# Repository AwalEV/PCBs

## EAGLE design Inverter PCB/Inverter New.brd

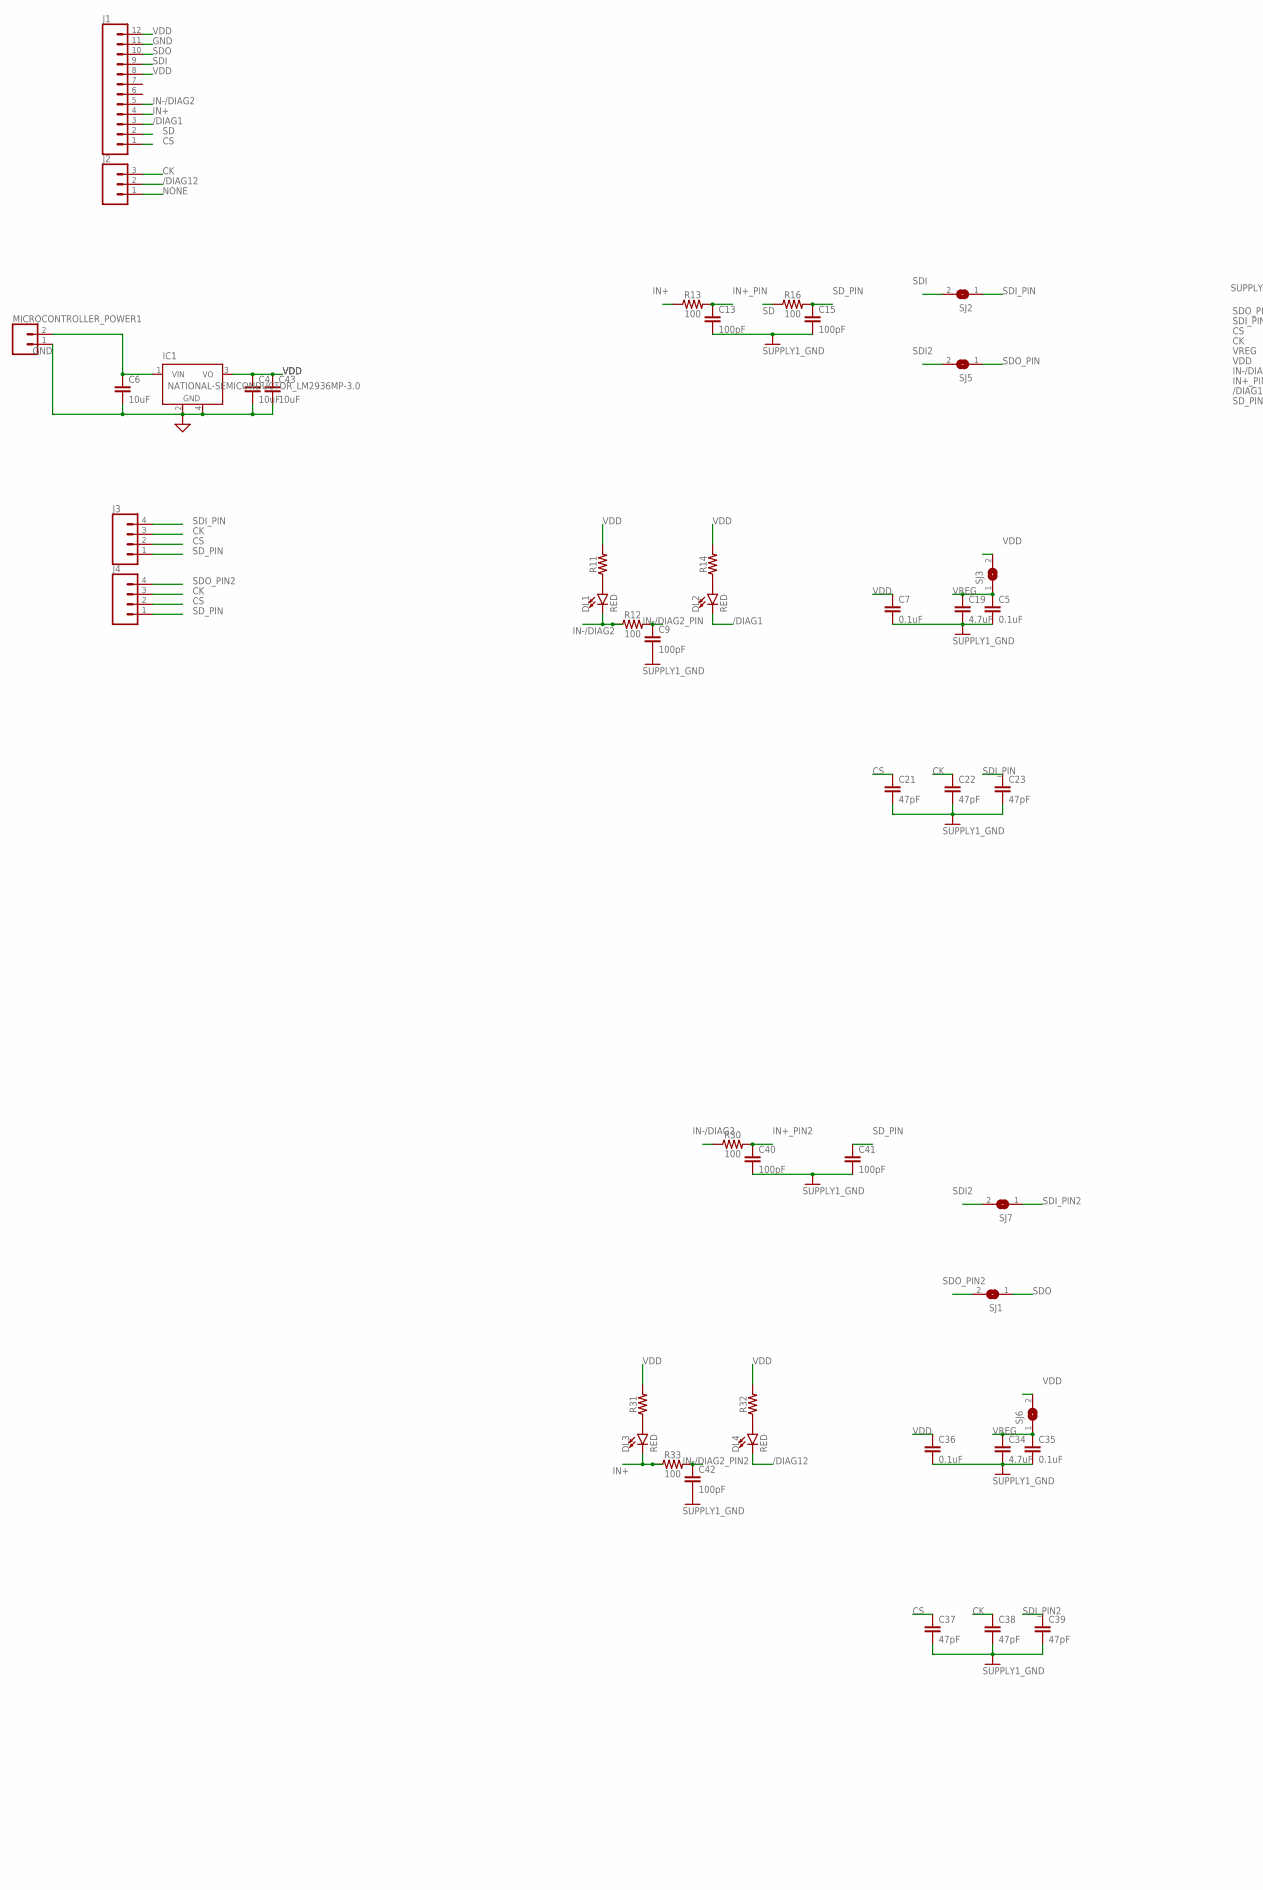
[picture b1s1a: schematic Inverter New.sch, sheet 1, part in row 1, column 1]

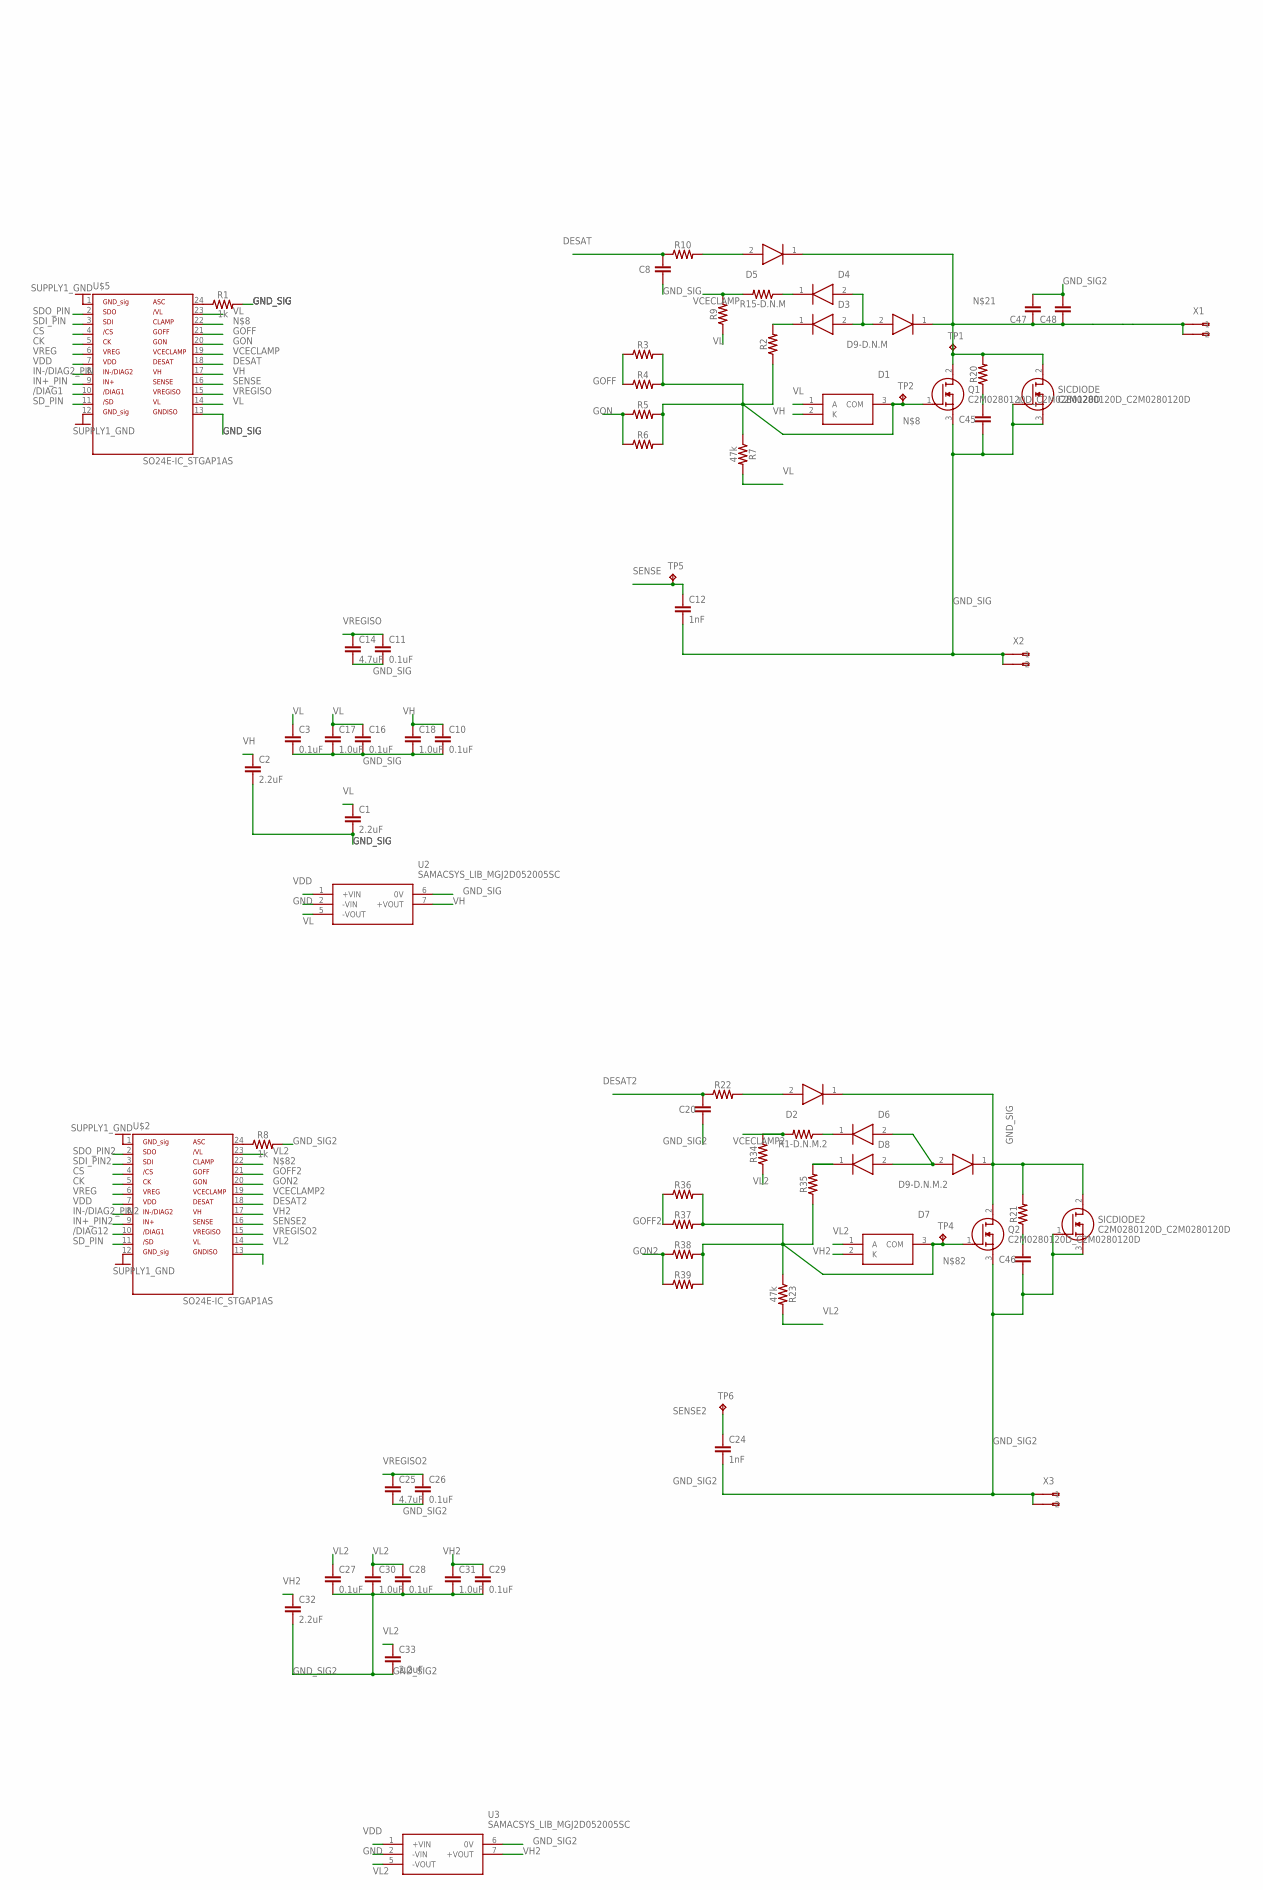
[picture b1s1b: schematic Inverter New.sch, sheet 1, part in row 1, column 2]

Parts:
C1, C2, C32, C33: 2.2uF; SPARKFUN-CAPACITORS_1206
C3, C5, C7, C10, C11, C16, C26, C27, C28, C29, C35, C36: 0.1uF; SPARKFUN-CAPACITORS_0603
C4, C6, C43: 10uF; SPARKFUN-CAPACITORS_1210
C8, C9, C13, C15, C20, C40, C41, C42, C45, C46: 100pF; SPARKFUN-CAPACITORS_0603
C12, C24: 1nF; SPARKFUN-CAPACITORS_0603
C14, C19, C25, C34: 4.7uF; SPARKFUN-CAPACITORS_0603
C17, C18, C30, C31: 1.0uF; SPARKFUN-CAPACITORS_0805
C21, C22, C23, C37, C38, C39: 47pF; SPARKFUN-CAPACITORS_0603
C47, C48: C-EU225-062X268; C225-062X268
D1, D7: BAT54SFILM_BAT54SFILM; BAT54SFILM_SOT105P242X150-3N
D2, D5: STTH112A_STTH112A; STTH112A_DIOM5126X265N
D3, D8, D9-D.N.M, D9-D.N.M.2: STPS2H100A_STPS2H100A; STPS2H100A_DIOM5126X265N
D4, D6: BAT20JFILM_BAT20JFILM; BAT20JFILM_SOD2512X113N
DL1, DL2, DL3, DL4: RED; SPARKFUN-LED_LED-1206
IC1: NATIONAL-SEMICONDUCTOR_LM2936MP-3.0; NATIONAL-SEMICONDUCTOR_SOT223
J1: SPARKFUN-CONNECTORS_CONN_12LONGPADS; SPARKFUN-CONNECTORS_1X12_LONGPADS
J2: SPARKFUN-CONNECTORS_CONN_03LONGPADS; SPARKFUN-CONNECTORS_1X03_LONGPADS
J3, J4: SPARKFUN-CONNECTORS_CONN_04LONGPADS; SPARKFUN-CONNECTORS_1X04_LONGPADS
MICROCONTROLLER_POWER1: SPARKFUN-CONNECTORS_CONN_025MM; SPARKFUN-CONNECTORS_SCREWTERMINAL-5MM-2
Q1, Q2: C2M0280120D_C2M0280120D; C2M0280120D_TO544P521X1594X2550-3P
R1, R8, R10, R22: 1k; SPARKFUN-RESISTORS_0603
R1-D.N.M.2, R9, R15-D.N.M, R34: 0; SPARKFUN-RESISTORS_0603
R2, R35: SPARKFUN-RESISTORS_0805
R3, R4, R5, R6, R20, R21, R36, R37, R38, R39: SPARKFUN-RESISTORS_1206
R7, R23: 47k; SPARKFUN-RESISTORS_0603
R11, R14, R31, R32: SPARKFUN-RESISTORS_0603
R12, R13, R16, R30, R33: 100; SPARKFUN-RESISTORS_0603
SICDIODE, SICDIODE2: C2M0280120D_C2M0280120D; C2M0280120D_TO544P521X1594X2550-3P
SJ1, SJ2, SJ3, SJ5, SJ6, SJ7: JUMPER_SJ
TP1, TP2, TP4, TP5, TP6: TPTP15SQ; TP15SQ
U2, U3: SAMACSYS_LIB_MGJ2D052005SC; SAMACSYS_LIB_MGJ2D_7-PIN-SIP
U$2, U$5: SO24E-IC_STGAP1AS; SO24E-IC_SO24W
X1, X2, X3: 234-502

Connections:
/DIAG1: DL2.C, J1.3, U$5.10 (/DIAG1)
/DIAG12: DL4.C, J2.2, U$2.10 (/DIAG1)
CK: C22.1, C38.1, J2.3, J3.3, J4.3, U$2.5 (CK), U$5.5 (CK)
CS: C21.1, C37.1, J1.1, J3.2, J4.2, U$2.4 (/CS), U$5.4 (/CS)
DESAT: C8.1, R10.1, U$5.18 (DESAT)
DESAT2: C20.1, R22.1, U$2.18 (DESAT)
GND: C4.2, C5.2, C6.2, C7.2, C9.2, C13.2, C15.2, C19.2, C21.2, C22.2, C23.2, C34.2, C35.2, C36.2, C37.2, C38.2, C39.2, C40.2, C41.2, C42.2, C43.2, IC1.2 (GND), IC1.4 (GND), J1.11, MICROCONTROLLER_POWER1.1, U2.2 (-VIN), U3.2 (-VIN), U$2.1 (GND_SIG), U$2.12 (GND_SIG), U$5.1 (GND_SIG), U$5.12 (GND_SIG); also elsewhere on the board
GND_SIG: C1.2, C2.2, C3.2, C8.2, C10.2, C11.2, C12.2, C14.2, C16.2, C17.2, C18.2, C45.2, D2.1 (K), D9-D.N.M.2.1 (K), Q1.3 (S), Q2.2 (D), R1.2, R21.2, SICDIODE.1 (G), SICDIODE.3 (S), SICDIODE2.2 (D), U2.6 (0V), U$5.13 (GNDISO), X2.A1 (-1), X2.A2 (-2)
GND_SIG2: C20.2, C24.2, C25.2, C26.2, C27.2, C28.2, C29.2, C30.2, C31.2, C32.2, C33.2, C46.2, C47.2, C48.2, Q2.3 (S), R8.2, SICDIODE2.1 (G), SICDIODE2.3 (S), U3.6 (0V), U$2.13 (GNDISO), X3.A1 (-1), X3.A2 (-2)
GOFF: R3.1, R4.1, U$5.21 (GOFF)
GOFF2: R36.1, R37.1, U$2.21 (GOFF)
GON: R5.1, R6.1, U$5.20 (GON)
GON2: R38.1, R39.1, U$2.20 (GON)
IN+: DL3.C, J1.4, R13.1, R33.1
IN+_PIN: C13.1, R13.2, U$5.9 (IN+)
IN+_PIN2: C40.1, R30.2, U$2.9 (IN+)
IN-/DIAG2: DL1.C, J1.5, R12.1, R30.1
IN-/DIAG2_PIN: C9.1, R12.2, U$5.8 (IN-/DIAG2)
IN-/DIAG2_PIN2: C42.1, R33.2, U$2.8 (IN-/DIAG2)
unnamed: R1.1, U$5.24 (ASC)
unnamed: DL1.A, R11.1
unnamed: DL2.A, R14.1
unnamed: D5.2 (A), R10.2
unnamed: D2.2 (A), R22.2
unnamed: D3.1 (K), R2.2
unnamed: D1.3 (COM), Q1.1 (G), R2.1, R3.2, R4.2, R5.2, R6.2, R7.1, TP2.TP, U$5.22 (CLAMP)
unnamed: C6.1, IC1.1 (VIN), MICROCONTROLLER_POWER1.2
unnamed: D8.1 (K), R35.2
unnamed: R8.1, U$2.24 (ASC)
unnamed: DL3.A, R31.1
unnamed: DL4.A, R32.1
unnamed: D4.1 (K), R15-D.N.M.1
unnamed: D3.2 (A), D4.2 (A), D9-D.N.M.2 (A)
unnamed: D6.1 (K), R1-D.N.M.2.1
unnamed: D6.2 (A), D8.2 (A), D9-D.N.M.2.2 (A)
unnamed: C47.1, C48.1, D5.1 (K), D9-D.N.M.1 (K), Q1.2 (D), R20.2, SICDIODE.2 (D), TP1.TP, X1.A1 (-1), X1.A2 (-2)
unnamed: C45.1, R20.1
unnamed: C46.1, R21.1
unnamed: D7.3 (COM), Q2.1 (G), R23.1, R35.1, R36.2, R37.2, R38.2, R39.2, TP4.TP, U$2.22 (CLAMP)
NONE: J2.1
SD: J1.2, R16.1
SDI: J1.9, SJ2.2
SDI2: SJ5.2, SJ7.2
SDI_PIN: C23.1, J3.4, SJ2.1, U$5.3 (SDI)
SDI_PIN2: C39.1, SJ7.1, U$2.3 (SDI)
SDO: J1.10, SJ1.1
SDO_PIN: SJ5.1, U$5.2 (SDO)
SDO_PIN2: J4.4, SJ1.2, U$2.2 (SDO); also elsewhere on the board
SD_PIN: C15.1, C41.1, J3.1, J4.1, R16.2, U$2.11 (/SD), U$5.11 (/SD)
SENSE: C12.1, TP5.TP, U$5.16 (SENSE)
SENSE2: C24.1, TP6.TP, U$2.16 (SENSE)
VCECLAMP: R9.2, R15-D.N.M.2, U$5.19 (VCECLAMP)
VCECLAMP2: R1-D.N.M.2.2, R34.2, U$2.19 (VCECLAMP)
VDD: C4.1, C7.1, C36.1, C43.1, IC1.3 (VO), J1.8, J1.12, R11.2, R14.2, R31.2, R32.2, SJ3.2, SJ6.2, U2.1 (+VIN), U3.1 (+VIN), U$2.7 (VDD), U$5.7 (VDD); also elsewhere on the board
VH: C2.1, C10.1, C18.1, D1.2 (K), U2.7 (+VOUT), U$5.17 (VH)
VH2: C29.1, C31.1, C32.1, D7.2 (K), U3.7 (+VOUT), U$2.17 (VH)
VL: C1.1, C3.1, C16.1, C17.1, D1.1 (A), R7.2, R9.1, U2.5 (-VOUT), U$5.14 (VL), U$5.23 (VL)
VL2: C27.1, C28.1, C30.1, C33.1, D7.1 (A), R23.2, R34.1, U3.5 (-VOUT), U$2.14 (VL), U$2.23 (VL)
VREG: C5.1, C19.1, C34.1, C35.1, SJ3.1, SJ6.1, U$2.6 (VREG), U$5.6 (VREG)
VREGISO: C11.1, C14.1, U$5.15 (VREGISO)
VREGISO2: C25.1, C26.1, U$2.15 (VREGISO)

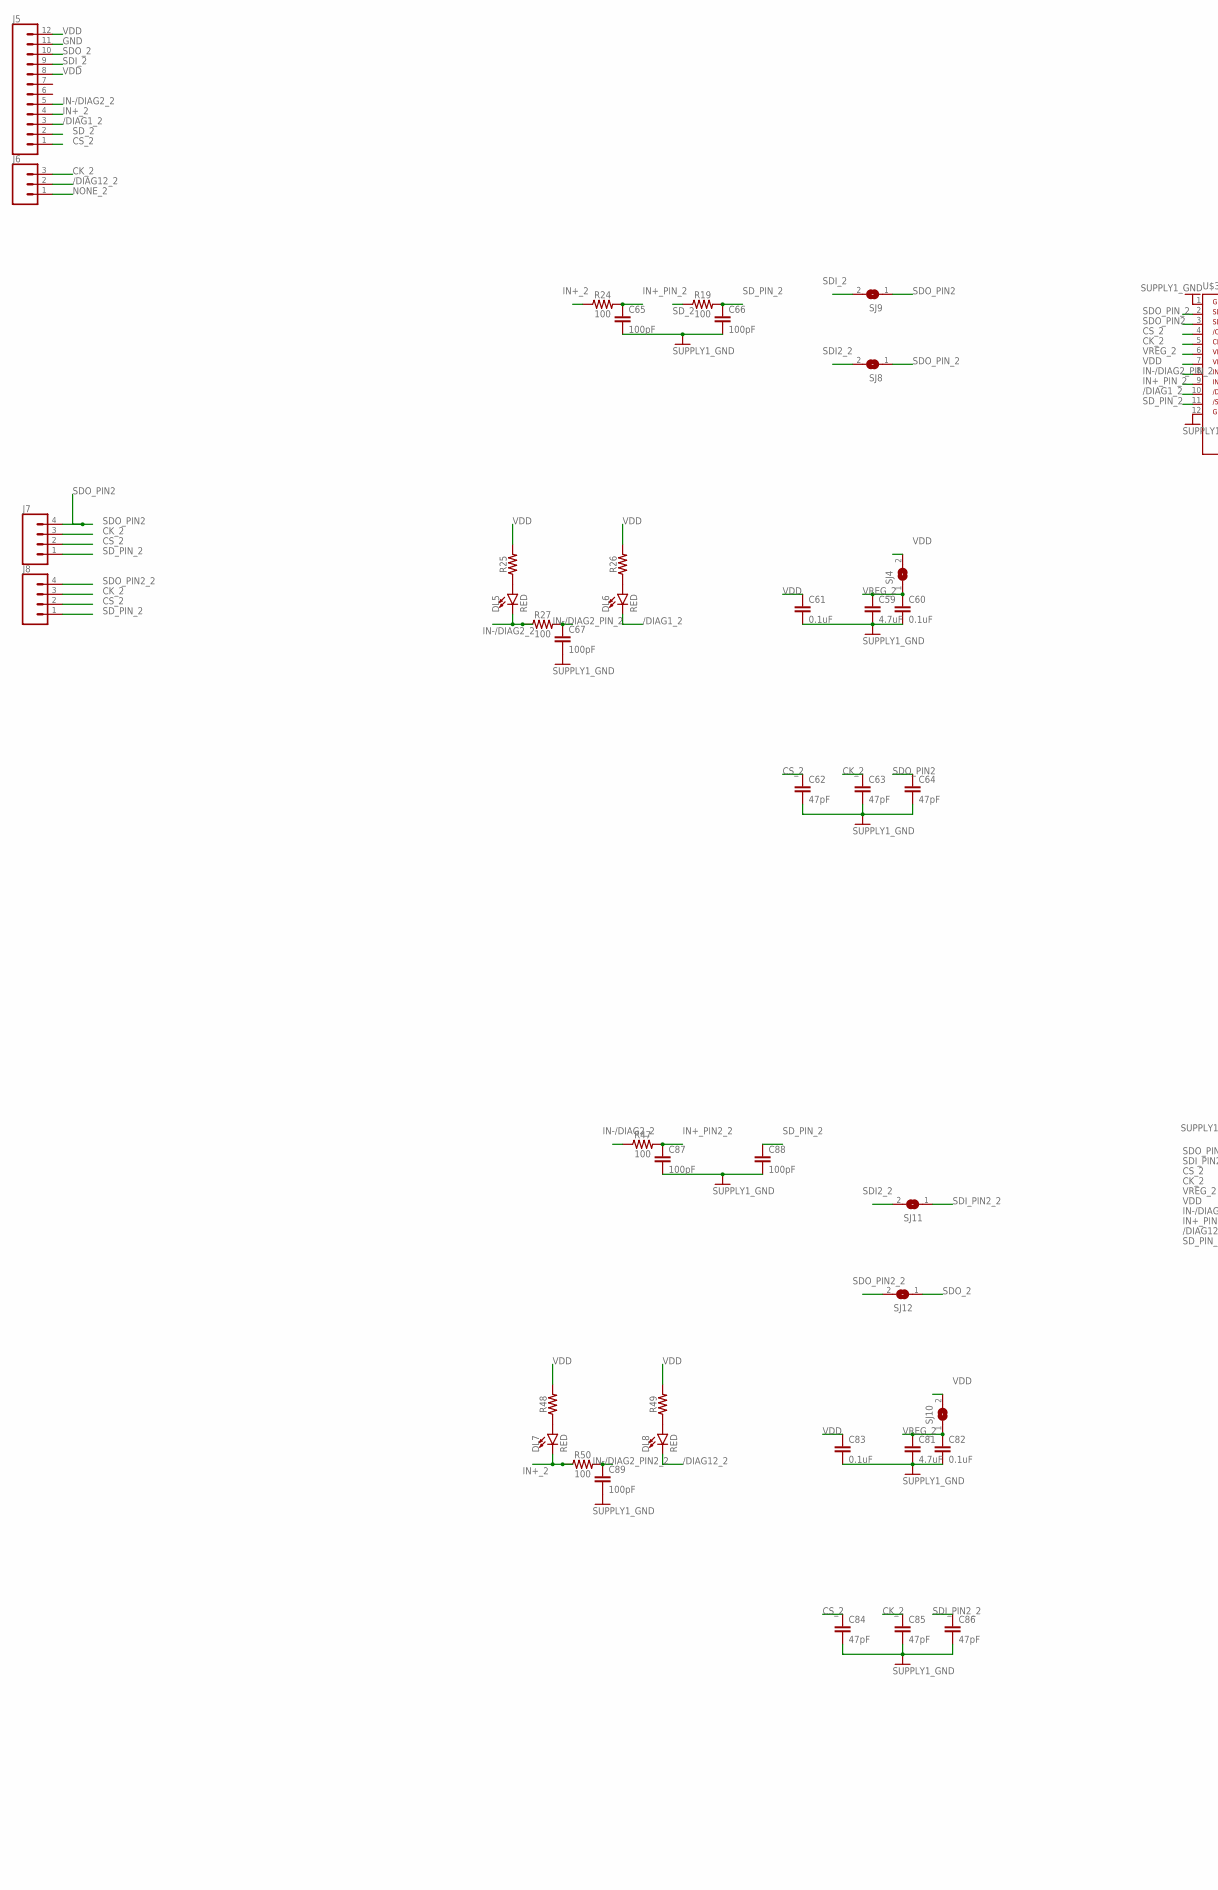
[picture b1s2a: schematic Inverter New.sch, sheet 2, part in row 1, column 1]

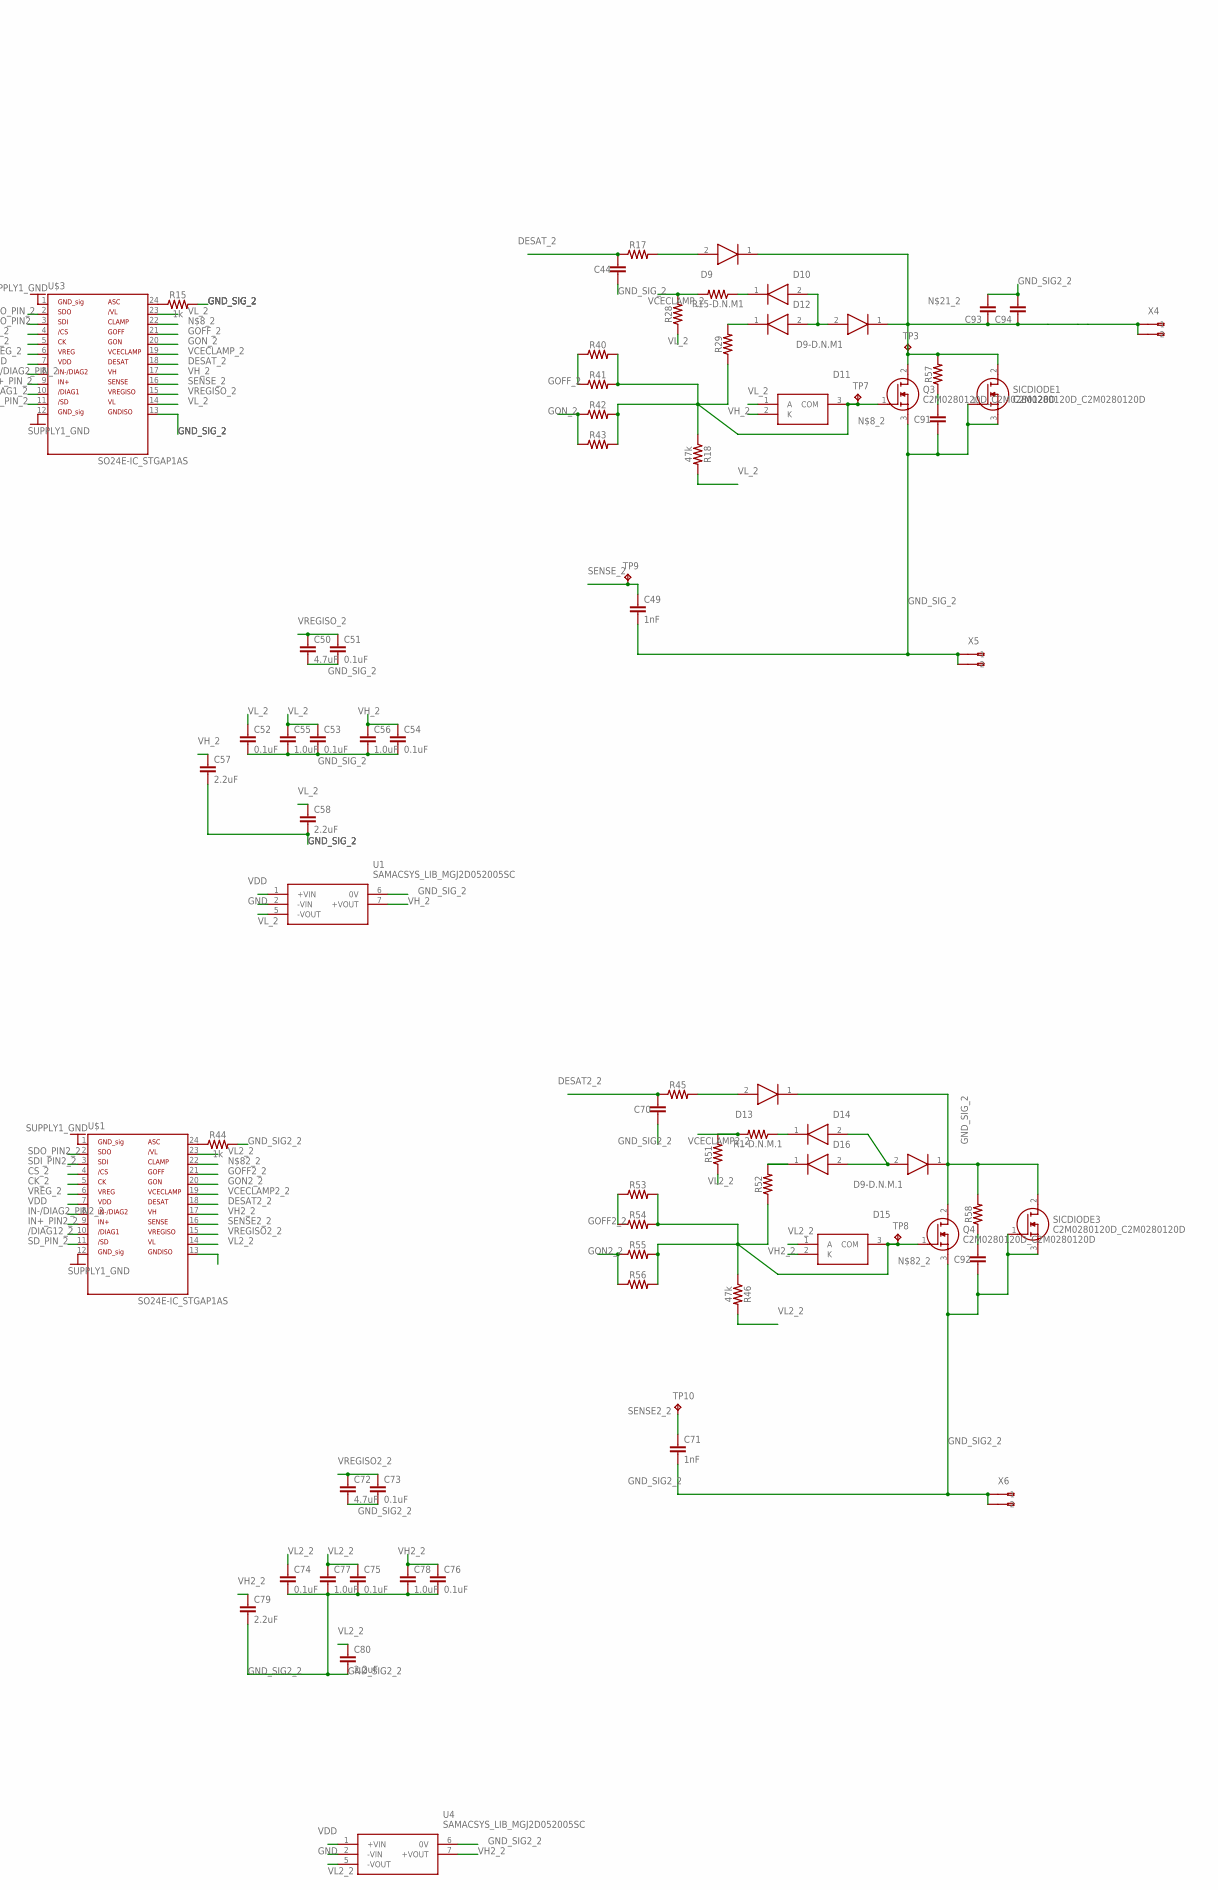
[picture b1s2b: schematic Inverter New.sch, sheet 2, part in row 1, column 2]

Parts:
C44, C65, C66, C67, C70, C87, C88, C89, C91, C92: 100pF; SPARKFUN-CAPACITORS_0603
C49, C71: 1nF; SPARKFUN-CAPACITORS_0603
C50, C59, C72, C81: 4.7uF; SPARKFUN-CAPACITORS_0603
C51, C52, C53, C54, C60, C61, C73, C74, C75, C76, C82, C83: 0.1uF; SPARKFUN-CAPACITORS_0603
C55, C56, C77, C78: 1.0uF; SPARKFUN-CAPACITORS_0805
C57, C58, C79, C80: 2.2uF; SPARKFUN-CAPACITORS_1206
C62, C63, C64, C84, C85, C86: 47pF; SPARKFUN-CAPACITORS_0603
C93, C94: C-EU225-062X268; C225-062X268
D9, D13: STTH112A_STTH112A; STTH112A_DIOM5126X265N
D9-D.N.M1, D9-D.N.M.1, D12, D16: STPS2H100A_STPS2H100A; STPS2H100A_DIOM5126X265N
D10, D14: BAT20JFILM_BAT20JFILM; BAT20JFILM_SOD2512X113N
D11, D15: BAT54SFILM_BAT54SFILM; BAT54SFILM_SOT105P242X150-3N
DL5, DL6, DL7, DL8: RED; SPARKFUN-LED_LED-1206
J5: SPARKFUN-CONNECTORS_CONN_12LONGPADS; SPARKFUN-CONNECTORS_1X12_LONGPADS
J6: SPARKFUN-CONNECTORS_CONN_03LONGPADS; SPARKFUN-CONNECTORS_1X03_LONGPADS
J7, J8: SPARKFUN-CONNECTORS_CONN_04LONGPADS; SPARKFUN-CONNECTORS_1X04_LONGPADS
Q3, Q4: C2M0280120D_C2M0280120D; C2M0280120D_TO544P521X1594X2550-3P
R1-D.N.M.1, R15-D.N.M1, R28, R51: 0; SPARKFUN-RESISTORS_0603
R15, R17, R44, R45: 1k; SPARKFUN-RESISTORS_0603
R18, R46: 47k; SPARKFUN-RESISTORS_0603
R19, R24, R27, R47, R50: 100; SPARKFUN-RESISTORS_0603
R25, R26, R48, R49: SPARKFUN-RESISTORS_0603
R29, R52: SPARKFUN-RESISTORS_0805
R40, R41, R42, R43, R53, R54, R55, R56, R57, R58: SPARKFUN-RESISTORS_1206
SICDIODE1, SICDIODE3: C2M0280120D_C2M0280120D; C2M0280120D_TO544P521X1594X2550-3P
SJ4, SJ8, SJ9, SJ10, SJ11, SJ12: JUMPER_SJ
TP3, TP7, TP8, TP9, TP10: TPTP15SQ; TP15SQ
U1, U4: SAMACSYS_LIB_MGJ2D052005SC; SAMACSYS_LIB_MGJ2D_7-PIN-SIP
U$1, U$3: SO24E-IC_STGAP1AS; SO24E-IC_SO24W
X4, X5, X6: 234-502

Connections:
/DIAG1_2: DL6.C, J5.3, U$3.10 (/DIAG1)
/DIAG12_2: DL8.C, J6.2, U$1.10 (/DIAG1)
CK_2: C63.1, C85.1, J6.3, J7.3, J8.3, U$1.5 (CK), U$3.5 (CK)
CS_2: C62.1, C84.1, J5.1, J7.2, J8.2, U$1.4 (/CS), U$3.4 (/CS)
DESAT2_2: C70.1, R45.1, U$1.18 (DESAT)
DESAT_2: C44.1, R17.1, U$3.18 (DESAT)
GND: C59.2, C60.2, C61.2, C62.2, C63.2, C64.2, C65.2, C66.2, C67.2, C81.2, C82.2, C83.2, C84.2, C85.2, C86.2, C87.2, C88.2, C89.2, J5.11, U1.2 (-VIN), U4.2 (-VIN), U$1.1 (GND_SIG), U$1.12 (GND_SIG), U$3.1 (GND_SIG), U$3.12 (GND_SIG); also elsewhere on the board
GND_SIG2_2: C70.2, C71.2, C72.2, C73.2, C74.2, C75.2, C76.2, C77.2, C78.2, C79.2, C80.2, C92.2, C93.2, C94.2, Q4.3 (S), R44.2, SICDIODE3.1 (G), SICDIODE3.3 (S), U4.6 (0V), U$1.13 (GNDISO), X6.A1 (-1), X6.A2 (-2)
GND_SIG_2: C44.2, C49.2, C50.2, C51.2, C52.2, C53.2, C54.2, C55.2, C56.2, C57.2, C58.2, C91.2, D9-D.N.M.1.1 (K), D13.1 (K), Q3.3 (S), Q4.2 (D), R15.2, R58.2, SICDIODE1.1 (G), SICDIODE1.3 (S), SICDIODE3.2 (D), U1.6 (0V), U$3.13 (GNDISO), X5.A1 (-1), X5.A2 (-2)
GOFF2_2: R53.1, R54.1, U$1.21 (GOFF)
GOFF_2: R40.1, R41.1, U$3.21 (GOFF)
GON2_2: R55.1, R56.1, U$1.20 (GON)
GON_2: R42.1, R43.1, U$3.20 (GON)
IN+_2: DL7.C, J5.4, R24.1, R50.1
IN+_PIN2_2: C87.1, R47.2, U$1.9 (IN+)
IN+_PIN_2: C65.1, R24.2, U$3.9 (IN+)
IN-/DIAG2_2: DL5.C, J5.5, R27.1, R47.1
IN-/DIAG2_PIN2_2: C89.1, R50.2, U$1.8 (IN-/DIAG2)
IN-/DIAG2_PIN_2: C67.1, R27.2, U$3.8 (IN-/DIAG2)
unnamed: D9.2 (A), R17.2
unnamed: D11.3 (COM), Q3.1 (G), R18.1, R29.1, R40.2, R41.2, R42.2, R43.2, TP7.TP, U$3.22 (CLAMP)
unnamed: D12.1 (K), R29.2
unnamed: DL5.A, R25.1
unnamed: C93.1, C94.1, D9.1 (K), D9-D.N.M1.1 (K), Q3.2 (D), R57.2, SICDIODE1.2 (D), TP3.TP, X4.A1 (-1), X4.A2 (-2)
unnamed: DL6.A, R26.1
unnamed: D13.2 (A), R45.2
unnamed: D16.1 (K), R52.2
unnamed: R44.1, U$1.24 (ASC)
unnamed: DL7.A, R48.1
unnamed: DL8.A, R49.1
unnamed: D9-D.N.M1.2 (A), D10.2 (A), D12.2 (A)
unnamed: D10.1 (K), R15-D.N.M1.1
unnamed: D9-D.N.M.1.2 (A), D14.2 (A), D16.2 (A)
unnamed: D14.1 (K), R1-D.N.M.1.1
unnamed: C91.1, R57.1
unnamed: C92.1, R58.1
unnamed: R15.1, U$3.24 (ASC)
unnamed: D15.3 (COM), Q4.1 (G), R46.1, R52.1, R53.2, R54.2, R55.2, R56.2, TP8.TP, U$1.22 (CLAMP)
NONE_2: J6.1
SDI2_2: SJ8.2, SJ11.2
SDI_2: J5.9, SJ9.2
SDI_PIN2_2: C86.1, SJ11.1, U$1.3 (SDI)
SDO_2: J5.10, SJ12.1
SDO_PIN2: C64.1, J7.4, SJ9.1, U$3.3 (SDI); also elsewhere on the board
SDO_PIN2_2: J8.4, SJ12.2, U$1.2 (SDO)
SDO_PIN_2: SJ8.1, U$3.2 (SDO)
SD_2: J5.2, R19.1
SD_PIN_2: C66.1, C88.1, J7.1, J8.1, R19.2, U$1.11 (/SD), U$3.11 (/SD)
SENSE2_2: C71.1, TP10.TP, U$1.16 (SENSE)
SENSE_2: C49.1, TP9.TP, U$3.16 (SENSE)
VCECLAMP2_2: R1-D.N.M.1.2, R51.2, U$1.19 (VCECLAMP)
VCECLAMP_2: R15-D.N.M1.2, R28.2, U$3.19 (VCECLAMP)
VDD: C61.1, C83.1, J5.8, J5.12, R25.2, R26.2, R48.2, R49.2, SJ4.2, SJ10.2, U1.1 (+VIN), U4.1 (+VIN), U$1.7 (VDD), U$3.7 (VDD); also elsewhere on the board
VH2_2: C76.1, C78.1, C79.1, D15.2 (K), U4.7 (+VOUT), U$1.17 (VH)
VH_2: C54.1, C56.1, C57.1, D11.2 (K), U1.7 (+VOUT), U$3.17 (VH)
VL2_2: C74.1, C75.1, C77.1, C80.1, D15.1 (A), R46.2, R51.1, U4.5 (-VOUT), U$1.14 (VL), U$1.23 (VL)
VL_2: C52.1, C53.1, C55.1, C58.1, D11.1 (A), R18.2, R28.1, U1.5 (-VOUT), U$3.14 (VL), U$3.23 (VL)
VREGISO2_2: C72.1, C73.1, U$1.15 (VREGISO)
VREGISO_2: C50.1, C51.1, U$3.15 (VREGISO)
VREG_2: C59.1, C60.1, C81.1, C82.1, SJ4.1, SJ10.1, U$1.6 (VREG), U$3.6 (VREG)

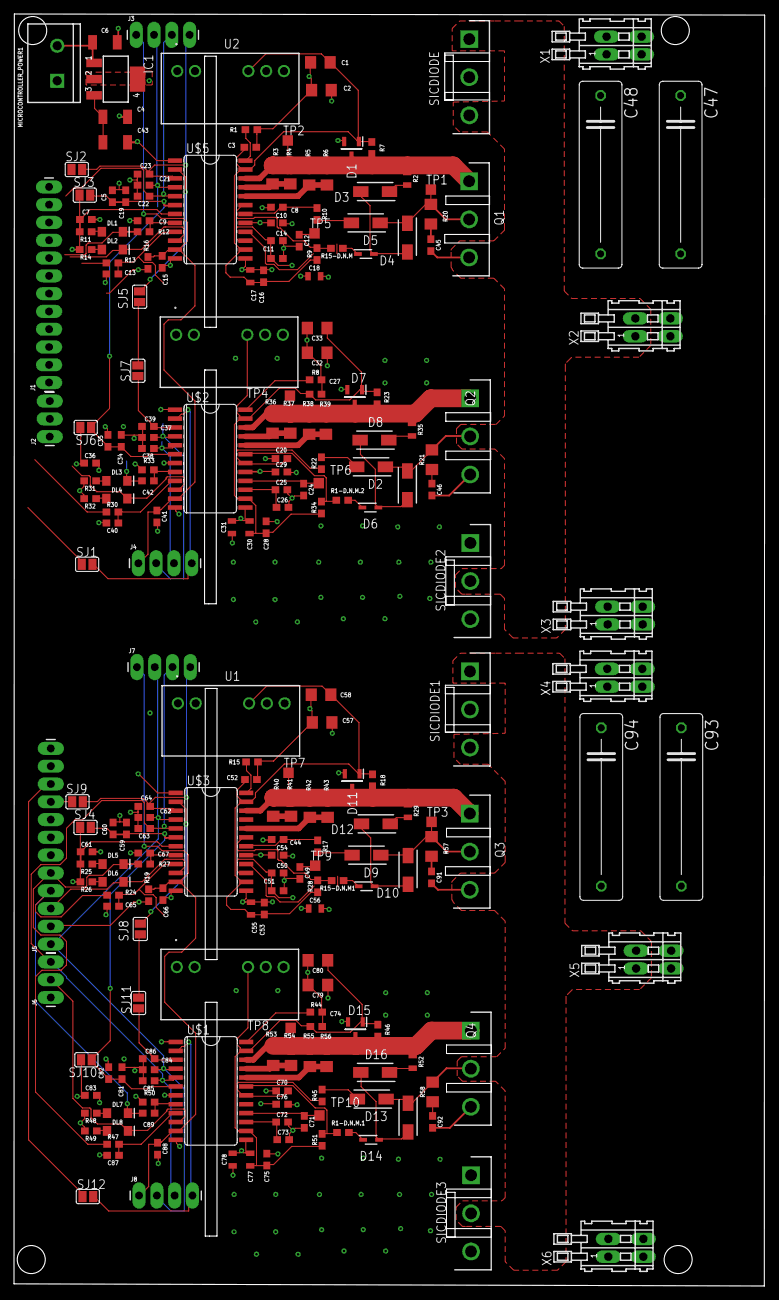
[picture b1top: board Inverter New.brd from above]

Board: 4 copper layers, 107.2 x 181.6 mm, 235 parts (0 on the bottom side), 116 nets.

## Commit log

2018-12-03 Inverter PCB Models
    Version 1
2018-12-07 PCB Design Update
    Adding the Bluetooth sensor
2018-12-07 PCB Update
    New URL
